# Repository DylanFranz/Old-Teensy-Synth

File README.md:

# Teensy-OP-1
Code and Hardware for my Teensy based Synth and Vocal FX Procesor

OUTDATED Check new repo on my page

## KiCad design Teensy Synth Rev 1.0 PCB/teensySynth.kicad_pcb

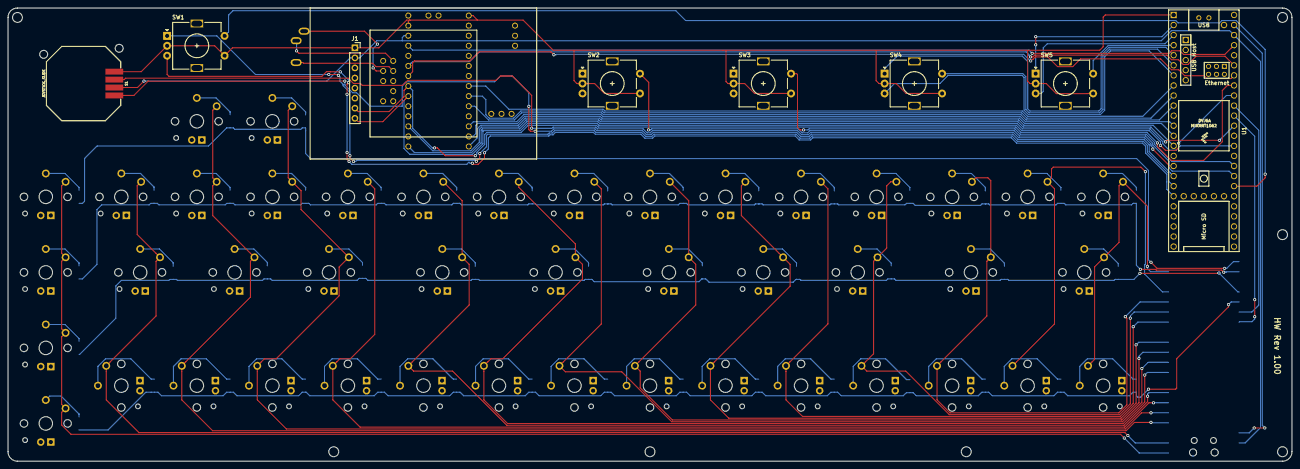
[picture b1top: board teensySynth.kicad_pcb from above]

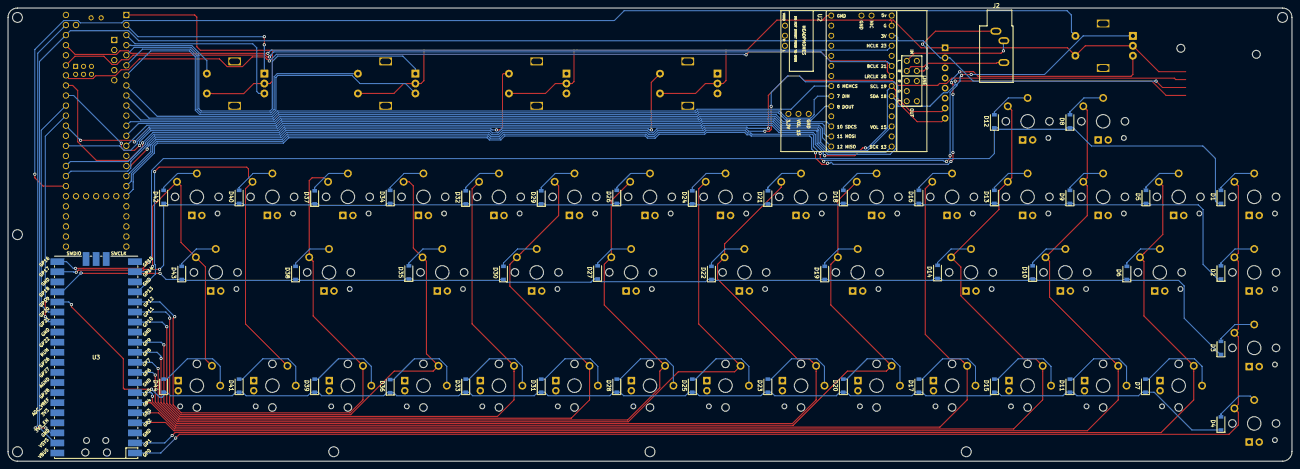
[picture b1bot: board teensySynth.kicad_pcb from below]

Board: 2 copper layers, 323.7 x 114.2 mm, 99 parts (47 on the bottom side), 97 nets.

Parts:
D1, D2, D3, D4, D5, D6, D7, D8, D9, D10, D11, D12, D13, D14, D15, D16, D17, D18, D19, D20, D21, D22, D23, D24, D25, D26, D27, D28, D29, D30, D31, D32, D33, D34, D35, D36, D37, D38, D39, D40, D41, D42, D43, D44: 1N4148W; D_SOD-123
J1: Conn_01x08; PinSocket_1x08_P2.54mm_Vertical
J2: AudioJack3; Jack_3.5mm_CUI_SJ1-3533NG_Horizontal
MX1, MX2, MX3, MX4, MX5, MX7, MX8, MX9, MX10, MX11, MX12, MX13, MX15, MX16, MX17, MX18, MX20, MX21, MX23, MX24, MX25, MX26, MX28, MX29, MX30, MX31, MX32, MX33, MX34, MX36, MX37, MX39, MX40, MX41, MX42, MX44: MX-NoLED; KailhChoc-1U
MX6, MX14, MX19, MX22, MX27, MX35, MX38, MX43: MX-NoLED; KailhChoc-1.5U
S1: JOYSTICK_SLIDE; JOYSTICK-PSP1000
SW1, SW2, SW3, SW4, SW5: Rotary_Encoder_Switch; Corrected_EC11
U1: Teensy4.1; Teensy41
U2: Teensy4.0_AudioShield_REVD; 4.0audioshield
U3: Pico; RPi_Pico_SMD_TH

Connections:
/3V3: J1.2, S1.VCC, U1.46, U2.28, U3.39
/BCLK: U1.43, U2.25
/COL0: MX1.1, MX2.1, MX3.1, MX4.1, U3.1
/COL1: MX5.1, MX6.1, MX7.1, U3.2
/COL2: MX8.1, MX9.1, MX10.1, MX11.1, U3.4
/COL3: MX12.1, MX13.1, MX14.1, MX15.1, U3.5
/COL4: MX16.1, MX17.1, U3.6
/COL5: MX18.1, MX19.1, MX20.1, U3.7
/COL6: MX21.1, MX22.1, MX23.1, U3.9
/COL7: MX24.1, MX25.1, U3.10
/COL8: MX26.1, MX27.1, MX28.1, U3.11
/COL9: MX29.1, MX30.1, MX31.1, U3.12
/COL10: MX32.1, MX33.1, U3.14
/COL11: MX34.1, MX35.1, MX36.1, U3.15
/COL12: MX37.1, MX38.1, MX39.1, U3.16
/COL13: MX40.1, MX41.1, U3.17
/COL14: MX42.1, MX43.1, MX44.1, U3.19
/DIN: U1.9, U2.9
/DOUT: U1.10, U2.10
/GND: J1.1, S1.GND, SW1.C, SW1.S1, SW2.C, SW2.S1, SW3.C, SW3.S1, SW4.C, SW4.S1, SW5.C, SW5.S1, U1.1, U2.1, U2.29
/JOY_X: S1.X, U1.17
/JOY_Y: S1.Y, U1.16
/LRCLK: U1.42, U2.24
/MCLK: U1.45, U2.27
/MEMCS: U1.8, U2.8
/MISO: U1.14, U2.14
/MOSI: U1.13, U2.13
/PIGND: U1.47, U3.38
/ROW0: D1.1, D8.1, D12.1, U3.21
/ROW1: D2.1, D5.1, D9.1, D13.1, D16.1, D18.1, D21.1, D24.1, D26.1, D29.1, D32.1, D34.1, D37.1, D40.1, D42.1, U3.22
/ROW2: D3.1, D6.1, D10.1, D14.1, D19.1, D22.1, D27.1, D30.1, D35.1, D38.1, D43.1, U3.24
/ROW3: D4.1, D7.1, D11.1, D15.1, D17.1, D20.1, D23.1, D25.1, D28.1, D31.1, D33.1, D36.1, D39.1, D41.1, D44.1, U3.25
/S1A: SW1.A, U1.18
/S1B: SW1.B, U1.19
/S4A: SW4.A, U1.5
/S4B: SW4.B, U1.7
/S5A: SW5.A, U1.2
/S5B: SW5.B, U1.3
/SCK: U1.35, U2.17
/SCL: J1.7, U1.41, U2.23
/SCL1: U1.38, U3.27
/SDA: J1.8, U1.40, U2.22
/SDA1: U1.39, U3.26
/SDCS: U1.12, U2.12
/SW1: SW1.S2, U1.31
/SW2: SW2.S2, U1.32
/SW3: SW3.S2, U1.33
/SW4: SW4.S2, U1.6
/SW5: SW5.S2, U1.4
/VOL: U1.37, U2.19
unnamed: D1.2, MX1.2
unnamed: D2.2, MX2.2
unnamed: D3.2, MX3.2
unnamed: D4.2, MX4.2
unnamed: D5.2, MX5.2
unnamed: D6.2, MX6.2
unnamed: D7.2, MX7.2
unnamed: D8.2, MX8.2
unnamed: D9.2, MX9.2
unnamed: D10.2, MX10.2
unnamed: D11.2, MX11.2
unnamed: D12.2, MX12.2
unnamed: D13.2, MX13.2
unnamed: D14.2, MX14.2
unnamed: D15.2, MX15.2
unnamed: D16.2, MX16.2
unnamed: D17.2, MX17.2
unnamed: D18.2, MX18.2
unnamed: D19.2, MX19.2
unnamed: D20.2, MX20.2
unnamed: D21.2, MX21.2
unnamed: D22.2, MX22.2
unnamed: D23.2, MX23.2
unnamed: D24.2, MX24.2
unnamed: D25.2, MX25.2
unnamed: D26.2, MX26.2
unnamed: D27.2, MX27.2
unnamed: D28.2, MX28.2
unnamed: D29.2, MX29.2
unnamed: D30.2, MX30.2
unnamed: D31.2, MX31.2
unnamed: D32.2, MX32.2
unnamed: D33.2, MX33.2
unnamed: D34.2, MX34.2
unnamed: D35.2, MX35.2
unnamed: D36.2, MX36.2
unnamed: D37.2, MX37.2
unnamed: D38.2, MX38.2
unnamed: D39.2, MX39.2
unnamed: D40.2, MX40.2
unnamed: D41.2, MX41.2
unnamed: D42.2, MX42.2
unnamed: D43.2, MX43.2
unnamed: D44.2, MX44.2
unnamed: J2.R, U2.34
unnamed: J2.S, U2.36
unnamed: J2.T, U2.35
